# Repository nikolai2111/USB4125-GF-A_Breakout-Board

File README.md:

# USB4125-GF-A_Breakout-Board <!-- omit from toc -->
## Content <!-- omit from toc -->
- [1. Description](#1-description)
- [2. Folder structure](#2-folder-structure)
- [3. Usage](#3-usage)
- [4. License](#4-license)

## 1. Description
This is a very simple and low level breakout board for the USB4125-GF-A a USB Type-C PD connector. Actually it's a breakout board for the footprint, with only the footprint on it, nothing else. The project was implemented with KiCAD, as single board or as a panel. It contains ready-to-use Gerber files for both, the single board and the panel (4x5 pcs.). For PCBWay Project click here (link not working, coming soon).

## 2. Folder structure
TBC

## 3. Usage
Add instructions and examples here.

## 4. License
The hardware and its documentation is licensed under the CERN-OHL-P licence, which can be found [here](LICENSE).

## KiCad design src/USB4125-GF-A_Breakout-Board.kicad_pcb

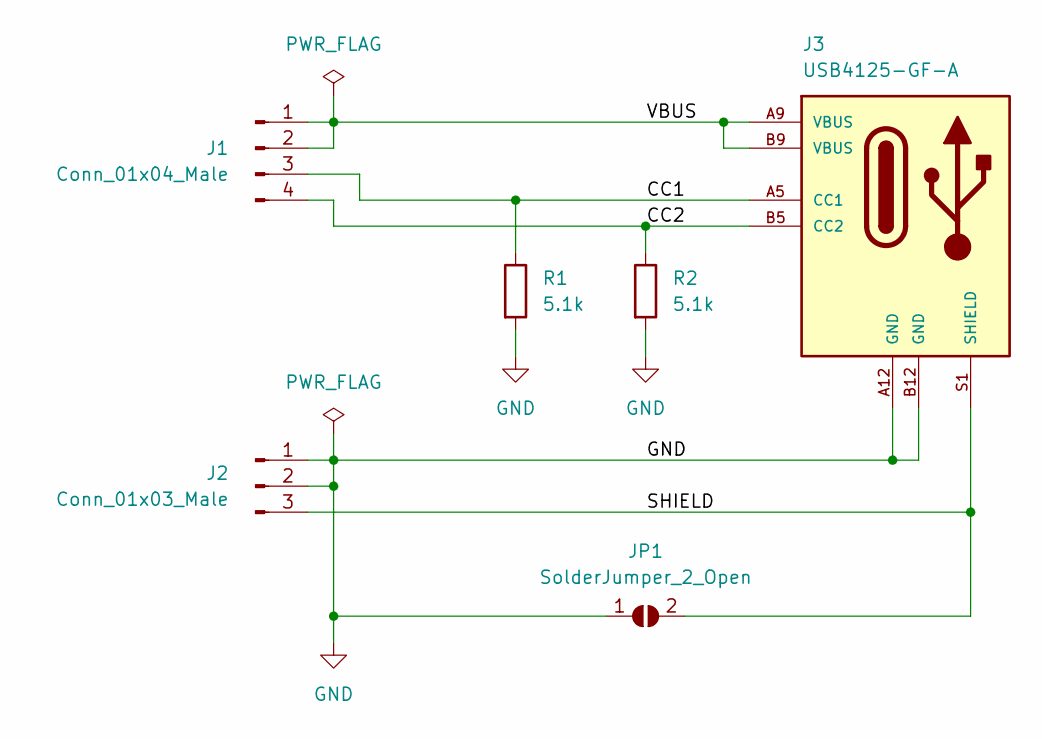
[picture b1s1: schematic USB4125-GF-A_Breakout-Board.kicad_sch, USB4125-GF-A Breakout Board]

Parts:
J1: Conn_01x04_Male; PinHeader_1x04_P2.54mm_Vertical
J2: Conn_01x03_Male; PinHeader_1x03_P2.54mm_Vertical
J3: USB4125-GF-A; GCT_USB4125-GF-A
JP1: SolderJumper_2_Open; SolderJumper-2_P1.3mm_Open_RoundedPad1.0x1.5mm
R1, R2: 5.1k; R_0805_2012Metric_Pad1.20x1.40mm_HandSolder

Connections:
/CC1: J1.3, J3.A5 (CC1), R1.1
/CC2: J1.4, J3.B5 (CC2), R2.1
/SHIELD: J2.3, J3.S1 (SHIELD), JP1.2 (B)
/VBUS: J1.1, J1.2, J3.A9 (VBUS), J3.B9 (VBUS)
GND: J2.1, J2.2, J3.A12 (GND), J3.B12 (GND), JP1.1 (A), R1.2, R2.2

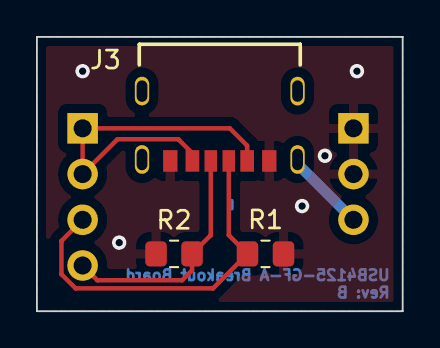
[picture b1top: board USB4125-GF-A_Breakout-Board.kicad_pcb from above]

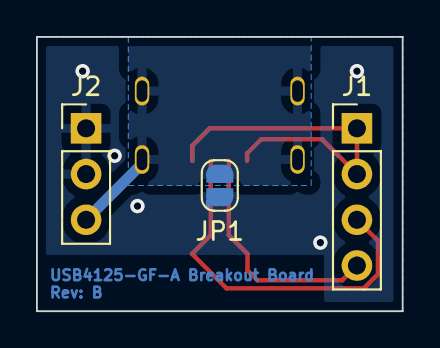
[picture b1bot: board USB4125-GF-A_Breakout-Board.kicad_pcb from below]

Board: 2 copper layers, 20.3 x 15.2 mm, 6 parts (3 on the bottom side), 5 nets.

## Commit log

2023-03-06 Add: Project and designed schmematics
2023-03-06 Mod: Finished project, updated schematic, added pcb and panel and exported data
2023-03-06 Add: Directory for the gerber files to .gitignore
2023-03-07 Mod: Updated the project name and revision to be on the copper layer now
2023-04-16 Mod: Moved some files
2023-04-25 Mod: Migrated to KiCAD 7.0
